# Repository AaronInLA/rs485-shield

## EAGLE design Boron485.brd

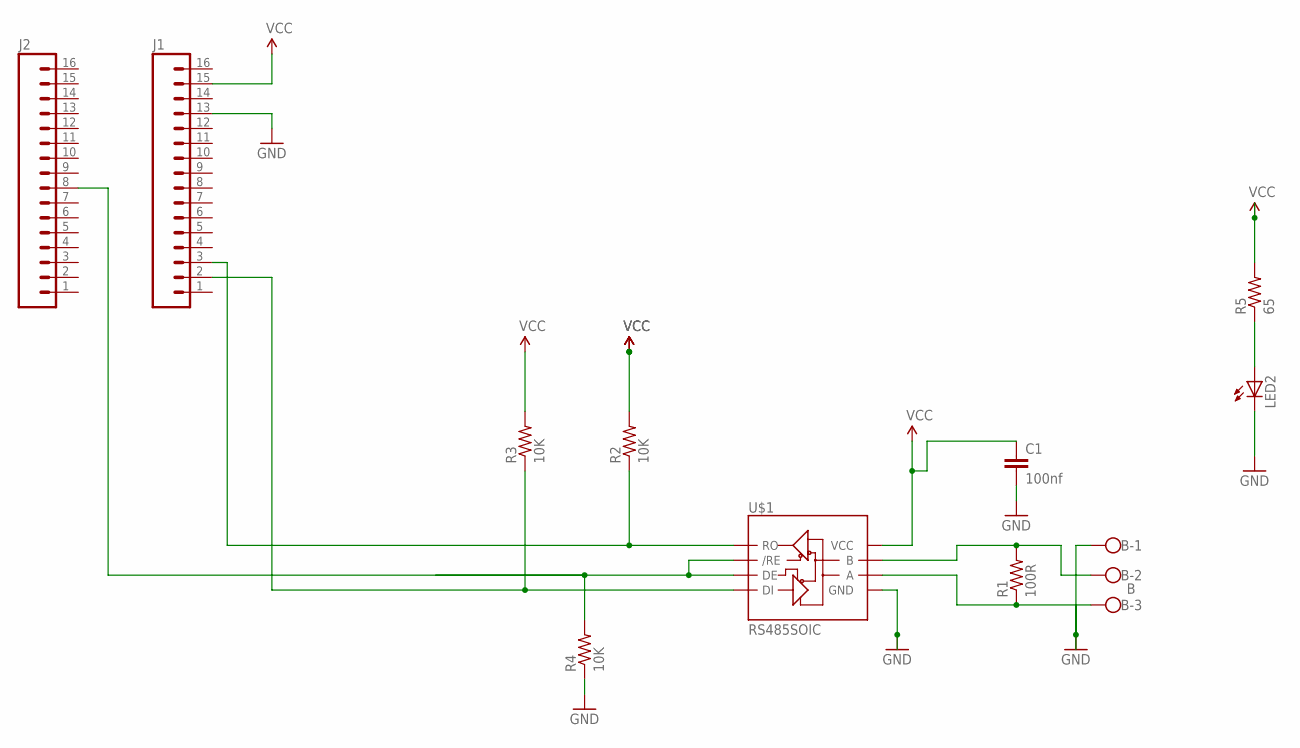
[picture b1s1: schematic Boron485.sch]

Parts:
B: B; W237-103
C1: 100nf; C0603
J1, J2: M16PTH; 1X16
LED2: LED_E; LED_1206
R1: 100R; 0603-RES
R2, R3, R4: 10K; 0603-RES
R5: 65; 0603-RES
U$1: RS485SOIC; SO08

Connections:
A: B.3, R1.1, U$1.6 (A)
B: B.2, R1.2, U$1.7 (B)
GND: B.1, C1.2, J1.13, LED2.C, R4.1, U$1.5 (GND)
R2LED: LED2.A, R5.1
RTS: J2.8, R4.2, U$1.2 (/RE), U$1.3 (DE)
RX: J1.3, R2.1, U$1.1 (RO)
TX: J1.2, R3.1, U$1.4 (DI)
VCC: C1.1, J1.15, R2.2, R3.2, R5.2, U$1.8 (VCC)

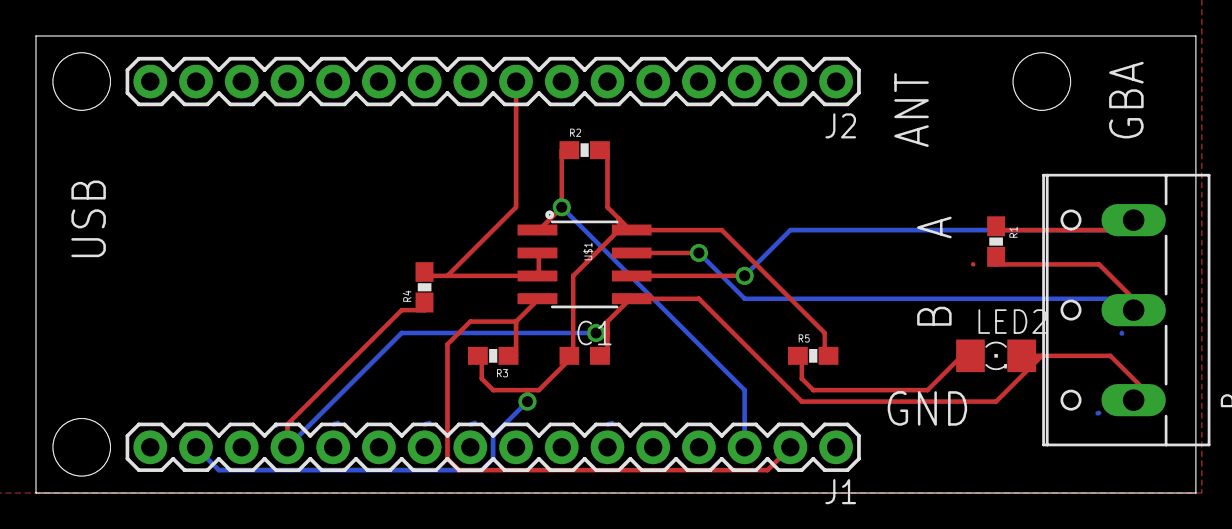
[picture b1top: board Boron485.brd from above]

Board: 2 copper layers, 64.4 x 25.4 mm, 11 parts (0 on the bottom side), 8 nets.

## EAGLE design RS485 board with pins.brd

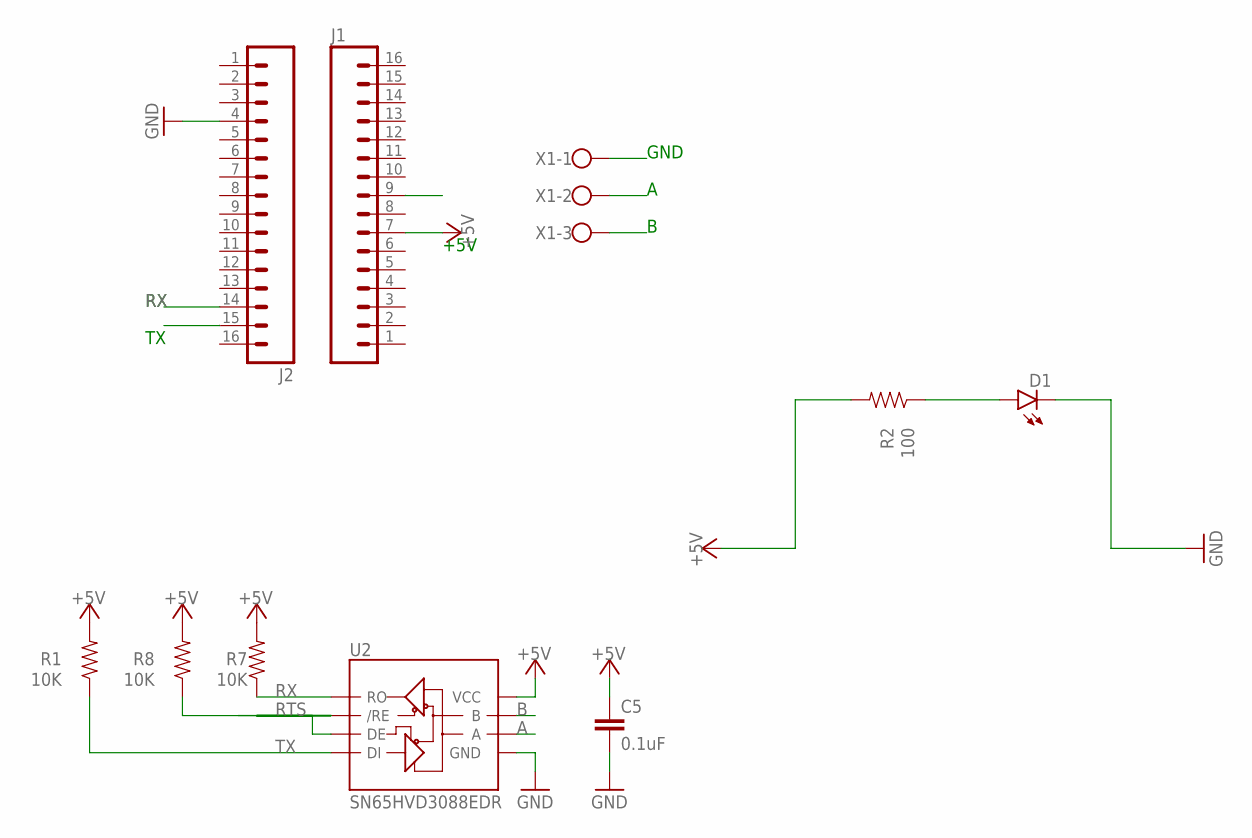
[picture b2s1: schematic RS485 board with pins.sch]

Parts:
C5: 0.1uF; 0603-CAP
D1: LED-FKIT-1206; FKIT-LED-1206
J1, J2: M16LOCK; 1X16_LOCK
R1, R7, R8: 10K; 0603-RES
R2: 100; 0603-RES
U2: SN65HVD3088EDR; SO08
X1: W237-103

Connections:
+5V: C5.1, J1.7, R1.2, R2.2, R7.2, R8.2, U2.8 (VCC)
A: U2.6 (A), X1.2
B: U2.7 (B), X1.3
GND: C5.2, D1.C, J2.4, U2.5 (GND), X1.1
unnamed: D1.A, R2.1
RTS: J1.9, R8.1, U2.2 (/RE), U2.3 (DE)
RX: J2.14, R7.1, U2.1 (RO)
TX: J2.15, R1.1, U2.4 (DI)

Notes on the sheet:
GND
+5V

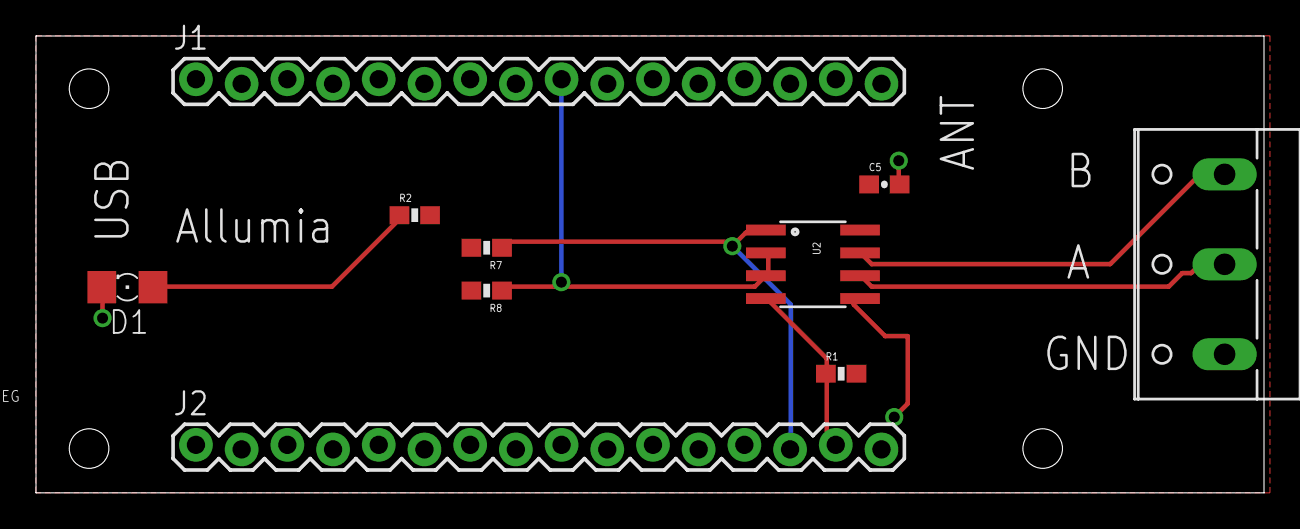
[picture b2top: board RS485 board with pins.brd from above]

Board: 2 copper layers, 68.2 x 25.4 mm, 10 parts (0 on the bottom side), 8 nets.

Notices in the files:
parts and their libraries:
SparkFun-Passives: Licensing: Creative Commons ShareAlike 4.0 International - https://creativecommons.org/licenses/by-sa/4.0
